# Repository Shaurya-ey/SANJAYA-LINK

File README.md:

<h1 align="center">SANJAYA-LINK</h1>

 ---

 # 1. Overview

SANJAYA-LINK is a custom 1-Watt telemetry and control system built for drones, fixed-wing UAVs, and RC models. While ELRS and crossfire modules are great, I wanted a transparent, fully customizable dev like board based on the RP2040 and SX1262 that I could integrate directly into my own flight controllers and ground stations.

## Features
- **RP2040** – Dual-core Cortex-M0+ microcontroller running up to 133 MHz. It handles all logic and communication.
- **SX1262** – LoRa transceiver for long-range, low-power wireless communication (EU bands).
- **0900FM15K0039001E** – RF crystal oscillator for stable timing.
- **W25Q128JVS** – 128 Mbit SPI flash memory for additional storage.
- **AP2112K-3.3** – 3.3V voltage regulator.
- **PE4259** – RF switch between antenna and transceiver.
- **Status LEDs** – For easier debugging or indication.
- **Dimensions:** - 51.82mm x 48.39mm

## What it is 
This is a custom-built, compact board that pairs the **RP2040 processor** with an **SX1262 LoRa radio**.
Basically, it's a long-range wireless communicator (through Radio Signals). I designed it to be a simple way to send data over long distances without needing Wi-Fi or any other mediums.

## Why I Made This Project
I was searching a solution for telemetery of data for my upcoming **Drone** and **Model Rocketry** ideas. Then i got deep into this idea and after researching a lot i found it intresting and do-able, and decided to build this from scratch. I’ve spent a lot of time debugging things like the clock settings and power rails to make sure it actually stays running on a battery which was hectic.

## How To Use
- **Connect:** Plug the module into your computer via the USB-C port to load your code.
- **Power:** You can run it off a battery or the USB supply; I’ve included a regulator to keep the power clean and stable.
- **Lesss Goo** Just write your script, upload it, and watch it start communicating over the LoRa network.

---

# 2. Layouts

## Schematics

## PCB

## Case And Assembly

<p align="center">

---

# 3. BOM (Bill Of Materials)

| Item | Description | Quantity | Total Price (USD) | URL |
|------|------------|----------|-------------------|-----|
| 100nF 0402 Capacitor | Ceramic capacitor 100nF 0402 package | 24 | 0.18 |https://robu.in/product/gcm155l8eh104ke07d-murata-electronics-50v-100nf-x8l-%c2%b110-0402-multilayer-ceramic-capacitors-mlcc-smd-smt-rohs/ |
| 1uF 0402 Capacitor | Ceramic capacitor 1uF 0402 package | 4 | 0.40 |https://www.digikey.in/en/products/detail/murata-electronics/GRM155R61H105ME05D/12091059 |
| 15pF 0402 Capacitor | Ceramic capacitor 15pF 0402 package | 5 | 0.12 |https://robu.in/product/gjm1555c1h150fb01d-murata-electronics-50v-15pf-c0g-%c2%b11-0402-multilayer-ceramic-capacitors-mlcc-smd-smt-rohs/ |
| 10uF 0402 Capacitor | Ceramic capacitor 10uF 0402 package | 4 | 1.04 | https://www.digikey.in/en/products/detail/murata-electronics/GRT155R61A106ME13D/19115561|
| 1nF 0402 Capacitor | Ceramic capacitor 1nF 0402 package | 2 | 0.28 |https://www.digikey.in/en/products/detail/kemet/C0402C102K5GECAUTO7411/8648675 |
| 39pF 0402 Capacitor | Ceramic capacitor 39pF 0402 package | 2 | 0.20 |https://www.digikey.in/en/products/detail/murata-electronics/GCM1555C1H390JA16J/4903596 |
| 3.3pF 0402 Capacitor | Ceramic capacitor 3.3pF 0402 package | 4 | 0.40 | https://www.digikey.in/en/products/detail/murata-electronics/GJM1555C1H3R3CB01D/702288|
| 470nF 0402 Capacitor | Ceramic capacitor 470nF 0402 package | 2 | 0.22 |https://www.digikey.in/en/products/detail/murata-electronics/GRM155R61A474KE15D/702528 |
| 47pF 0402 Capacitor | Ceramic capacitor 47pF 0402 package | 4 | 0.12 |https://robu.in/product/gcm1555c1h470fa16d-murata-electronics-50v-47pf-c0g-%c2%b11-0402-multilayer-ceramic-capacitors-mlcc-smd-smt-rohs/ |
| Blue LED 0402 | Blue indicator LED | 2 | 0.38 |https://www.digikey.in/en/products/detail/w%C3%BCrth-elektronik/150080BS75000/4489912 |
| Red LED 0402 | Red indicator LED | 2 | 0.38 |https://www.digikey.in/en/products/detail/w%C3%BCrth-elektronik/150080SS75000/4489921 |
| BLM15AX102SN1D | Ferrite bead 1kΩ @100MHz 0402 | 2 | 0.20 | https://www.digikey.in/en/products/detail/murata-electronics/BLM15AX102SN1D/2256877|
| 0900FM15K0039001E | LoRa RF front-end filter | 2 | 0.90 |https://www.digikey.in/en/products/detail/johanson-technology-inc/0900FM15K0039001E/16639329 |
| USB-C Port | USB Type-C receptacle | 2 | 1.54 |https://www.digikey.in/en/products/detail/gct/USB4105-GF-A/11198441 |
| SMA Connector | RF antenna connector | 2 | 6.56 |https://www.digikey.in/en/products/detail/taoglas-limited/EMPCB-SMAFSTJ-B-HT/3522337 |
| 15uH 0402 Inductor | Power inductor 15uH | 2 | 0.12 |https://www.digikey.in/en/products/detail/murata-electronics/LQW15DN150M00D/9559544 |
| 47nH 0402 Inductor | RF inductor 47nH | 2 | 0.20 | https://www.digikey.in/en/products/detail/murata-electronics/LQG15WH47NJ02D/11690059|
| 9.1nH 0402 Inductor | RF inductor 9.1nH | 4 | 0.13 |https://robu.in/product/lqw15an9n1g00d-murata-wirewound-inductor-9-1-nh-0-14-ohm-5-5-ghz-540-ma-0402-1005-metric-lqw15a_00/ |
| 100Ω 0402 Resistor | Resistor 100Ω | 2 | 0.20 | https://www.digikey.in/en/products/detail/yageo/RC0402FR-10100RL/16982189|
| 10kΩ 0402 Resistor | Resistor 10kΩ | 2 | 0.20 |https://www.digikey.in/en/products/detail/yageo/RT0402FRD0710KL/5926329 |
| 27.4Ω 0402 Resistor | Resistor 27.4Ω | 4 | 0.40 |https://www.digikey.in/en/products/detail/bourns-inc/CR0402-FX-27R4GLF/3783281 |
| 1kΩ 0402 Resistor | Resistor 1kΩ | 8 | 0.79 |https://www.digikey.in/en/products/detail/yageo/RC0402FR-071KL/726513 |
| 5.1kΩ 0402 Resistor | Resistor 5.1kΩ | 4 | 0.40 |https://www.digikey.in/en/products/detail/yageo/RC0402FR-135K1L/14286364 |
| Tactile Switch | Reset / Boot tactile switch | 4 | 0.88 |https://www.digikey.in/en/products/detail/same-sky-formerly-cui-devices/TS09-63-25-WT-260-SMT-TR/15839064 |
| SX1262IMLTRT | LoRa transceiver IC | 2 | 6.22 |https://robu.in/product/sx1262imltrt-semitech-300kbps-general-purposeism1ghz-spi-qfn-24-ep4x4-rf-transceiver-ics-rohs/ |
| RP2040 | Microcontroller | 2 | 1.74 |https://robu.in/product/raspberry-pi-rp2040/ |
| W25Q64JVSSIQ | SPI Flash memory | 2 | 4.40 |https://robu.in/product/w25q64jvssiq-winbond-elec-sop-8-208mil-nor-flash-rohs/ |
| AP2127K-3.3 | 3.3V LDO regulator | 2 | 0.38 |https://www.digikey.in/en/products/detail/diodes-incorporated/AP2127K-3-3TRG1/4470786 |
| RF Switch SPDT | RF switch SC70-6 | 2 | 1.56 |https://www.digikey.in/en/products/detail/psemi/4259-63/2614473 |
| 32MHz Crystal | System clock crystal | 2 | 0.88 | https://robu.in/product/yxc-ysx221sl-32mhz-12pf-20ppm-4pad-smd-smt-crystal/|
| 12MHz Crystal | System clock crystal | 2 | 0.40 |https://robu.in/product/ysx321sl-12mhz-10pf-10ppm-4pins-smd-smt-metal-surface-quartz-crystal-pack-of-2/ |
| Schottky Diode | Fast switching diode | 2 | 0.46 |https://www.digikey.in/en/products/detail/mcc-micro-commercial-components/MBR0520-TP/717250 |
| USBLC6-2SC6 | USB ESD protection | 2 | 0.70 | https://www.digikey.in/en/products/detail/stmicroelectronics/USBLC6-2SC6/1040559|
| TPD1E05U06 | ESD protection diode | 2 | 0.70 | https://www.digikey.in/en/products/detail/texas-instruments/TPD1E05U06DPYR/3844805|
| MF-MSMF050 | Resettable fuse | 2 | 1.02 | https://www.digikey.in/en/products/detail/bourns-inc/MF-MSMF050-30X-2/15926789|
| Header Pins | Pin headers | 2 | 0.13 |https://robu.in/product/2-54mm-1x40-pin-male-single-row-straight-short-header-strip-pack-of-3/ |
| 865–868MHz Antenna | Rubber duck antenna | 1 | 0.69 | https://robu.in/product/865-868mhz-1-8-dbi-gain-rubber-duck-antenna/|
| Solder Wire | Soldering wire | 1 | 3.30 | https://robu.in/product/soldering-wire-1-mm-100g/|
| Soldering Flux | Flux for soldering | 1 | 3.24 |https://www.amazon.in/dp/B08VHD1VS1?ref=cm_sw_r_cso_wa_apan_dp_CBZ3XEAZ58AZ3J60TK4D&ref_=cm_sw_r_cso_wa_apan_dp_CBZ3XEAZ58AZ3J60TK4D&social_share=cm_sw_r_cso_wa_apan_dp_CBZ3XEAZ58AZ3J60TK4D |
| Tip Tinner | Soldering tip cleaner | 1 | 5.41 |https://www.amazon.in/dp/B09BQRQ9JF?ref=cm_sw_r_cso_wa_apan_dp_LIGHTSABER1XE9YXXVSO&ref_=cm_sw_r_cso_wa_apan_dp_LIGHTSABER1XE9YXXVSO&social_share=cm_sw_r_cso_wa_apan_dp_LIGHTSABER1XE9YXXVSO |
| Hot Air Station | YIHUA 8858-IV portable | 1 | 25.09 |https://robu.in/product/yihua-8858-iv-portable-hot-air-station/ |
| PCB Manufacturing + 3-D Printing | Printed circuit board + 3d printing | 1 | 24.14 + 2 | |
| 2.5x10mm Screws | Screws for Case | 1 | 1.52 | https://robu.in/product/easymech-ss-304-csk-countersunk-philips-head-m2-5-x-6-mm-bolt-25-pcs/ |
| **Shipping** | **Shipping fee** | 1 | 13.01 | |
| **TOTAL** |  |  | **116.17 USD** | |

# Note:
- I want some Soldering items + Heat gun for Soldering SMD components (as Assembly as a option for PCB Manufacturing is very costly + there will be hefty custom fees on them for 2 assembled boards), that i've included in BOM.
- I've included everything including Total Shipping Fee and Cart screen shots in the BOM.
- I'm building 2 LoRa boards so that i can verify and use them in my future projects.

**Thank You!!**

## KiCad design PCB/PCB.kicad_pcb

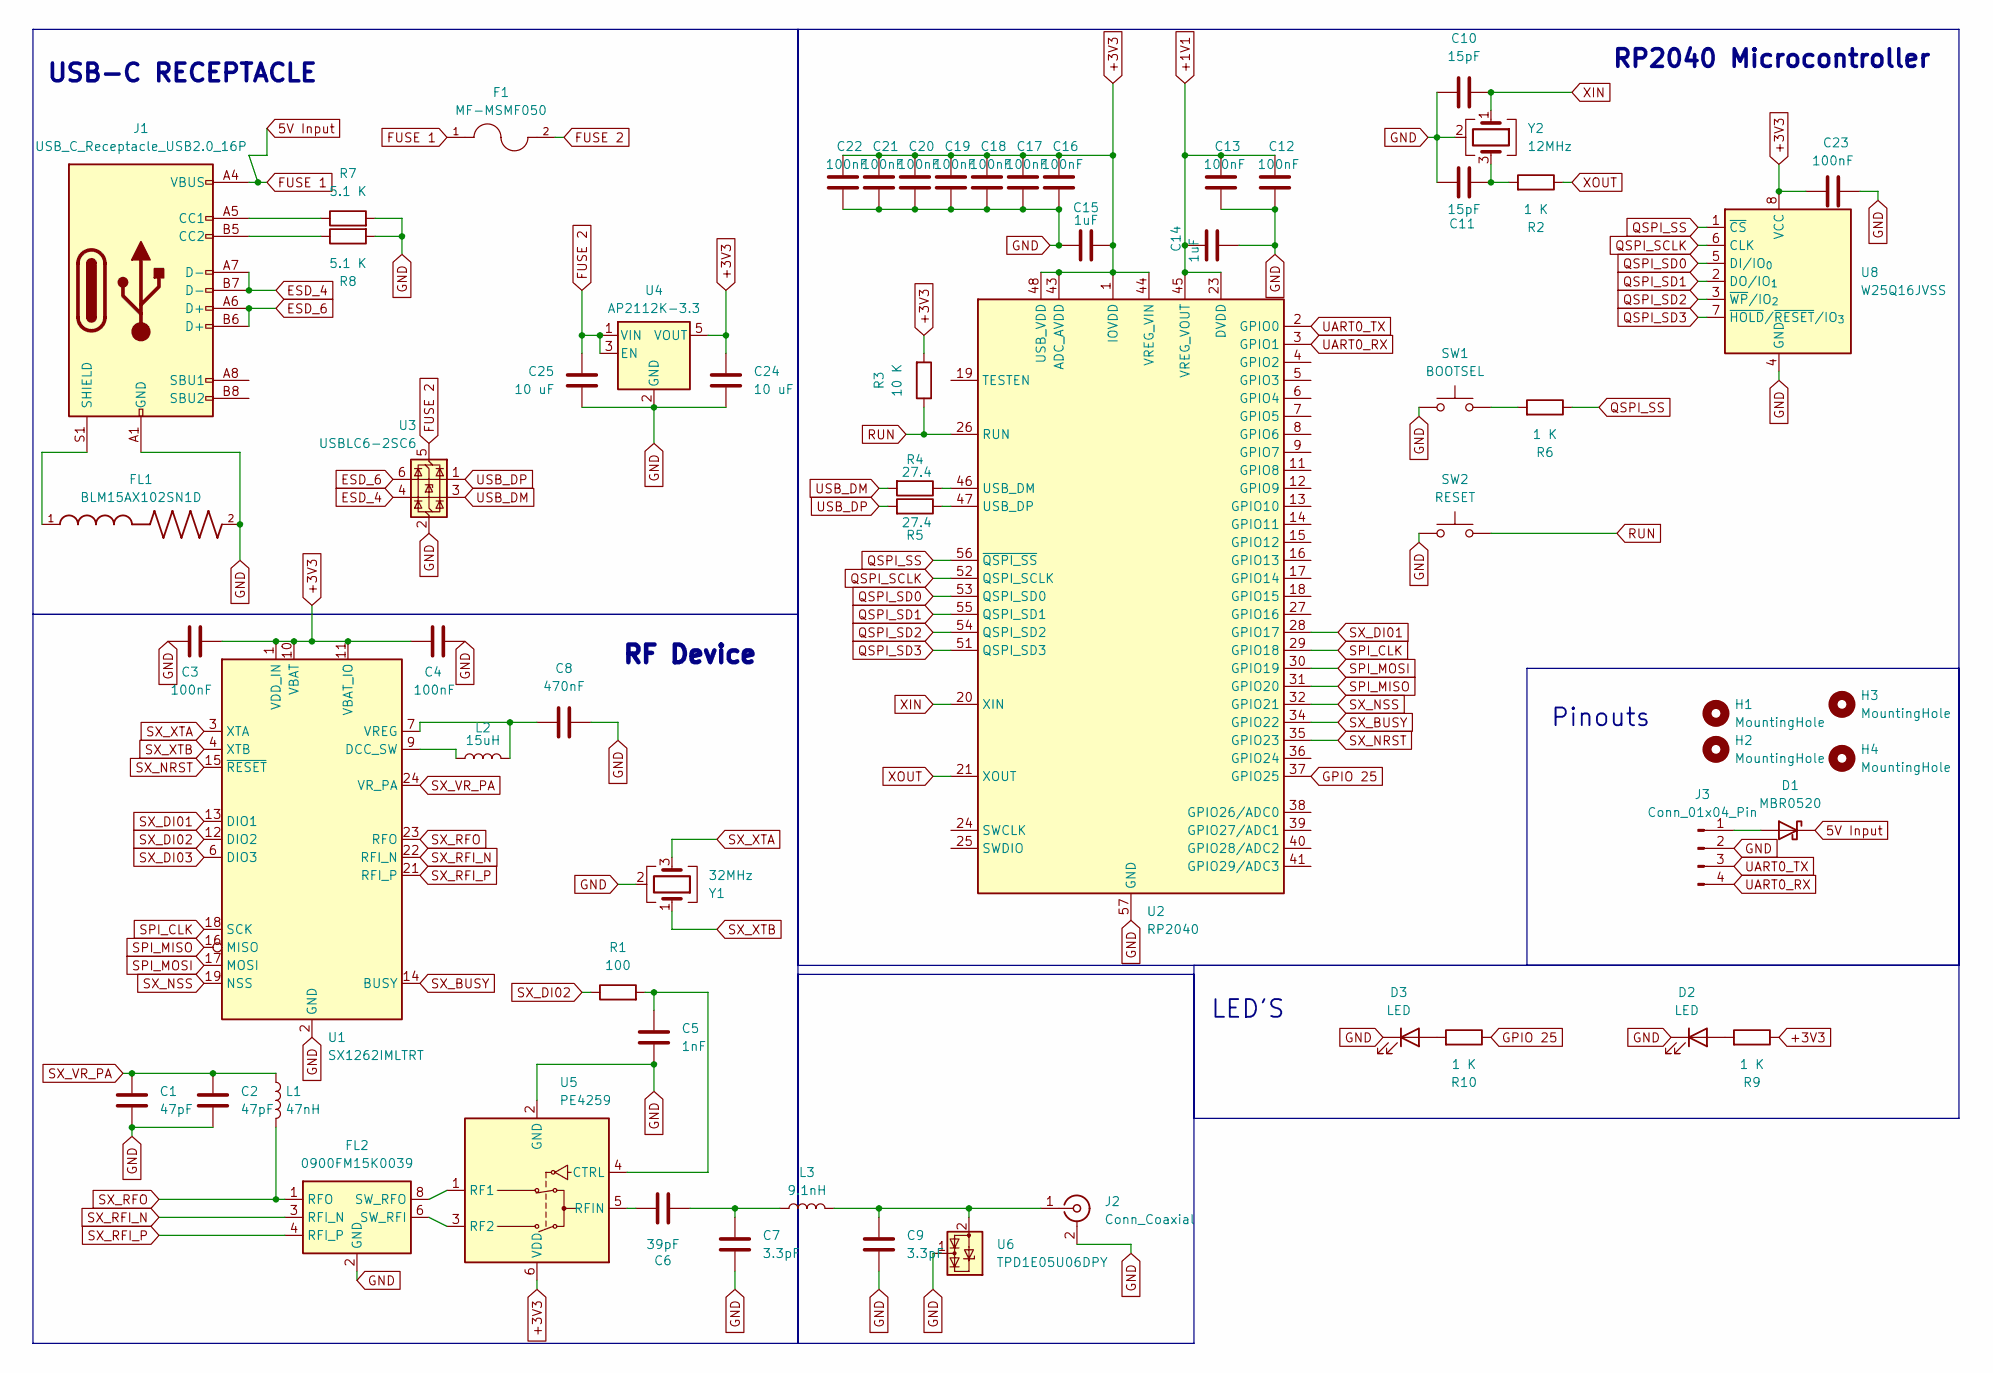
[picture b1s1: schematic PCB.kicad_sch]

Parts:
C1, C2: 47pF; C_0402_1005Metric
C3, C4, C12, C13, C16, C17, C18, C19, C20, C21, C22, C23: 100nF; C_0402_1005Metric
C5: 1nF; C_0402_1005Metric
C6: 39pF; C_0402_1005Metric
C7, C9: 3.3pF; C_0402_1005Metric
C8: 470nF; C_0402_1005Metric
C10, C11: 15pF; C_0402_1005Metric
C14, C15: 1uF; C_0402_1005Metric
C24, C25: 10 uF; C_0402_1005Metric
D1: MBR0520; D_SOD-123
D2, D3: LED; LED_0805_2012Metric
F1: MF-MSMF050; FUSER_MF-MSMF050
FL1: BLM15AX102SN1D; L_0402_1005Metric
FL2: 0900FM15K0039; Balun_Johanson_0900FM15K0039
H1, H2, H3, H4: MountingHole; MountingHole_2.7mm_M2.5_Pad
J1: USB_C_Receptacle_USB2.0_16P; USB_C_Receptacle_GCT_USB4105-xx-A_16P_TopMnt_Horizontal
J2: Conn_Coaxial; SMA_Molex_73251-1153_EdgeMount_Horizontal
J3: Conn_01x04_Pin; PinHeader_1x04_P2.54mm_Vertical
L1: 47nH; L_0402_1005Metric
L2: 15uH; L_0402_1005Metric
L3: 9.1nH; L_0402_1005Metric
R1: 100; R_0402_1005Metric
R2, R6, R9, R10: 1 K; R_0402_1005Metric
R3: 10 K; R_0402_1005Metric
R4, R5: 27.4; R_0402_1005Metric
R7, R8: 5.1 K; R_0402_1005Metric
SW1: BOOTSEL; SW_Tactile_SPST_NO_Straight_CK_PTS636Sx25SMTRLFS
SW2: RESET; SW_Tactile_SPST_NO_Straight_CK_PTS636Sx25SMTRLFS
U1: SX1262IMLTRT; QFN-24-1EP_4x4mm_P0.5mm_EP2.6x2.6mm
U2: RP2040; QFN-56-1EP_7x7mm_P0.4mm_EP3.2x3.2mm
U3: USBLC6-2SC6; SOT-23-6
U4: AP2112K-3.3; SOT-23-5
U5: PE4259; SOT-363_SC-70-6
U6: TPD1E05U06DPY; Texas_DPY0002A_0.6x1mm_P0.65mm
U8: W25Q16JVSS; SOIC-8_5.3x5.3mm_P1.27mm
Y1: 32MHz; Crystal_SMD_3225-4Pin_3.2x2.5mm
Y2: 12MHz; Crystal_SMD_Abracon_ABM8G-4Pin_3.2x2.5mm

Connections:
5V Input: D1.1 (K), F1.1, J1.A4 (VBUS), J1.A9 (VBUS), J1.B4 (VBUS), J1.B9 (VBUS)
+1V1: C12.2, C13.2, C14.2, U2.23 (DVDD), U2.45 (VREG_VOUT), U2.50 (DVDD)
+3V3: C3.2, C4.1, C15.2, C16.2, C17.2, C18.2, C19.2, C20.2, C21.2, C22.2, C23.1, C24.1, R3.2, R9.1, U1.1 (VDD_IN), U1.10 (VBAT), U1.11 (VBAT_IO), U2.1 (IOVDD), U2.10 (IOVDD), U2.22 (IOVDD), U2.33 (IOVDD), U2.42 (IOVDD), U2.43 (ADC_AVDD), U2.44 (VREG_VIN), U2.48 (USB_VDD), U2.49 (IOVDD), U4.5 (VOUT), U5.6 (VDD), U8.8 (VCC)
ESD_4: J1.A7 (D-), J1.B7 (D-), U3.4 (I/O2)
ESD_6: J1.A6 (D+), J1.B6 (D+), U3.6 (I/O1)
FUSE 2: C25.1, F1.2, U3.5 (VBUS), U4.1 (VIN), U4.3 (EN)
GND: C1.2, C2.2, C3.1, C4.2, C5.2, C7.2, C8.2, C9.2, C10.1, C11.1, C12.1, C13.1, C14.1, C15.1, C16.1, C17.1, C18.1, C19.1, C20.1, C21.1, C22.1, C23.2, C24.2, C25.2, D2.1 (K), D3.1 (K), FL1.2, FL2.2 (GND), FL2.5 (GND), FL2.7 (GND), FL2.9 (GND), FL2.10 (GND), J1.A1 (GND), J1.A12 (GND), J1.B1 (GND), J1.B12 (GND), J2.2 (Ext), J3.2, R7.2, R8.2, SW1.1, SW2.1, U1.2 (GND), U1.5 (GND), U1.8 (GND), U1.20 (GND), U1.25 (GND), U2.57 (GND), U3.2 (GND), U4.2 (GND), U5.2 (GND), U6.1 (I/O), U8.4 (GND), Y1.2 (G), Y1.4 (G), Y2.2 (G), Y2.4 (G)
GPIO 25: R10.1, U2.37 (GPIO25)
unnamed: C6.2, C7.1, L3.1
unnamed: C11.2, R2.2, Y2.3
unnamed: D1.2 (A), J3.1
unnamed: D2.2 (A), R9.2
unnamed: D3.2 (A), R10.2
unnamed: FL2.6 (SW_RFI), U5.3 (RF2)
unnamed: FL2.8 (SW_RFO), U5.1 (RF1)
unnamed: J1.A5 (CC1), R7.1
unnamed: J1.B5 (CC2), R8.1
unnamed: FL1.1, J1.S1 (SHIELD)
unnamed: C9.1, J2.1 (In), L3.2, U6.2 (GND)
unnamed: R6.2, SW1.2
unnamed: L2.1, U1.9 (DCC_SW)
unnamed: C8.1, L2.2, U1.7 (VREG)
unnamed: R4.1, U2.46 (USB_DM)
unnamed: R5.1, U2.47 (USB_DP)
unnamed: C5.1, R1.2, U5.4 (CTRL)
unnamed: C6.1, U5.5 (RFIN)
QSPI_SCLK: U2.52 (QSPI_SCLK), U8.6 (CLK)
QSPI_SD0: U2.53 (QSPI_SD0), U8.5 (DI/IO_{0})
QSPI_SD1: U2.55 (QSPI_SD1), U8.2 (DO/IO_{1})
QSPI_SD2: U2.54 (QSPI_SD2), U8.3 (~WP/IO_{2})
QSPI_SD3: U2.51 (QSPI_SD3), U8.7 (~HOLD/~RESET/IO_{3})
QSPI_SS: R6.1, U2.56 (~QSPI_SS), U8.1 (~CS)
RUN: R3.1, SW2.2, U2.26 (RUN)
SPI_CLK: U1.18 (SCK), U2.29 (GPIO18)
SPI_MISO: U1.16 (MISO), U2.31 (GPIO20)
SPI_MOSI: U1.17 (MOSI), U2.30 (GPIO19)
SX_BUSY: U1.14 (BUSY), U2.34 (GPIO22)
SX_DI01: U1.13 (DIO1), U2.28 (GPIO17)
SX_DI02: R1.1, U1.12 (DIO2)
SX_DI03: U1.6 (DIO3)
SX_NRST: U1.15 (~RESET), U2.35 (GPIO23)
SX_NSS: U1.19 (NSS), U2.32 (GPIO21)
SX_RFI_N: FL2.3 (RFI_N), U1.22 (RFI_N)
SX_RFI_P: FL2.4 (RFI_P), U1.21 (RFI_P)
SX_RFO: FL2.1 (RFO), L1.2, U1.23 (RFO)
SX_VR_PA: C1.1, C2.1, L1.1, U1.24 (VR_PA)
SX_XTA: U1.3 (XTA), Y1.3
SX_XTB: U1.4 (XTB), Y1.1
UART0_RX: J3.4, U2.3 (GPIO1)
UART0_TX: J3.3, U2.2 (GPIO0)
USB_DM: R4.2, U3.3 (I/O2)
USB_DP: R5.2, U3.1 (I/O1)
XIN: C10.2, U2.20 (XIN), Y2.1
XOUT: R2.1, U2.21 (XOUT)

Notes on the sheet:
LED'S
RF Device
RP2040 Microcontroller
USB-C RECEPTACLE
Pinouts

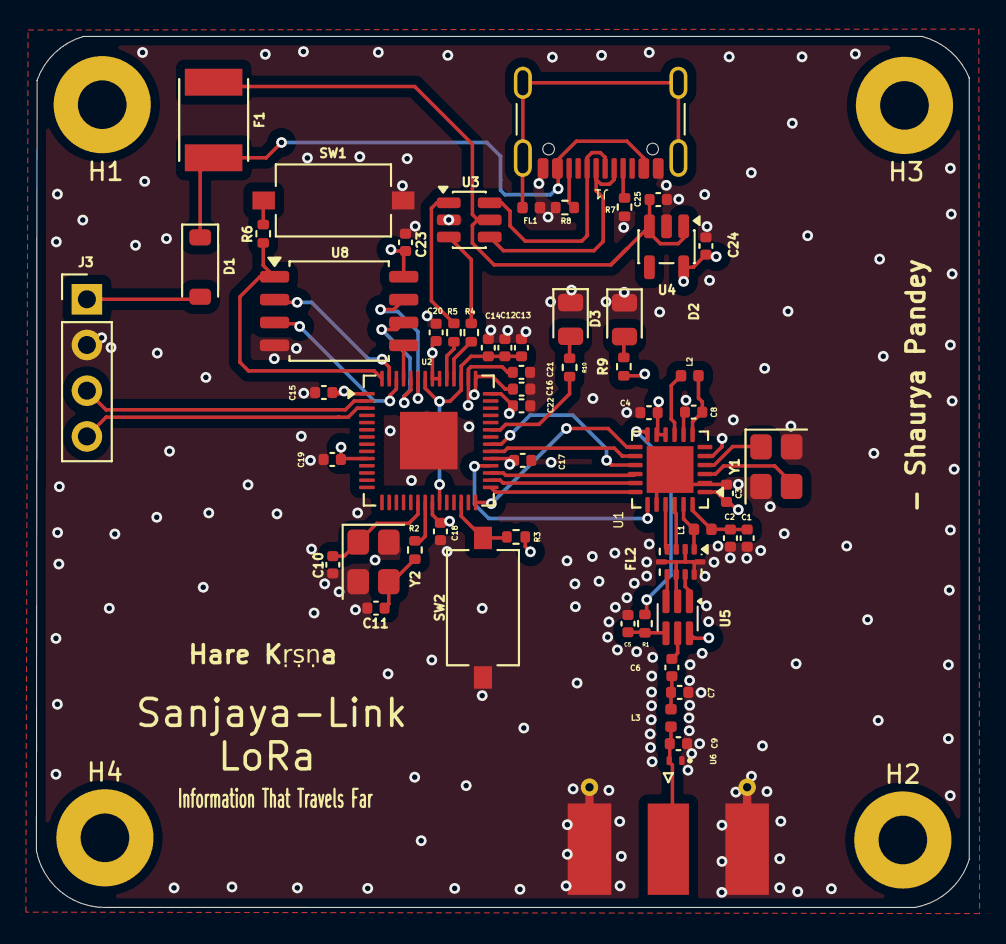
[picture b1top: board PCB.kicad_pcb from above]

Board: 4 copper layers, 51.8 x 48.4 mm, 62 parts (0 on the bottom side), 53 nets.

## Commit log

2026-03-09 Add schematic image to README
2026-03-09 Rename Schematic.PNG to temp
2026-03-09 Create TEMP
2026-03-10 Rename project in README.md
    Updated project name from SANJAYA-LINK to VIDURA-LINK in README.
2026-03-10 Update README with VIDURA-LINK overview
    Added a brief overview of the VIDURA-LINK system.
2026-03-10 Update README with schematic and clean up images
    Added schematic image to README and removed duplicate PCB images.
2026-03-10 Fix image tag for pcbback in README
    Updated image tag for pcbback in README.md.
2026-03-10 Adjust image dimensions in README
    Updated image sizes for better display.
2026-03-10 Update image dimensions and alignment in README
2026-03-10 Add project motivation to README
    Added a section explaining the motivation behind the project.
2026-03-10 Fix formatting of Overview section in README
    Removed space before '1. Overview' in README.
2026-03-10 Fix formatting and heading in README.md
    Corrected formatting for the overview section and updated heading levels.
2026-03-10 Revise README formatting and overview section
    Updated formatting and improved the overview section.
2026-03-10 Fix image height in README.md
2026-03-10 Replace back PCB image in README
2026-03-10 Update README.md for clarity and corrections
    Corrected typos and improved clarity in the project description.
2026-03-10 Enhance features section with bold text
    Updated features section with bold formatting for clarity.
2026-03-10 Fix typos and enhance project overview in README
    Corrected typos and improved clarity in the project description.
2026-03-10 Fix formatting and typos in README.md
